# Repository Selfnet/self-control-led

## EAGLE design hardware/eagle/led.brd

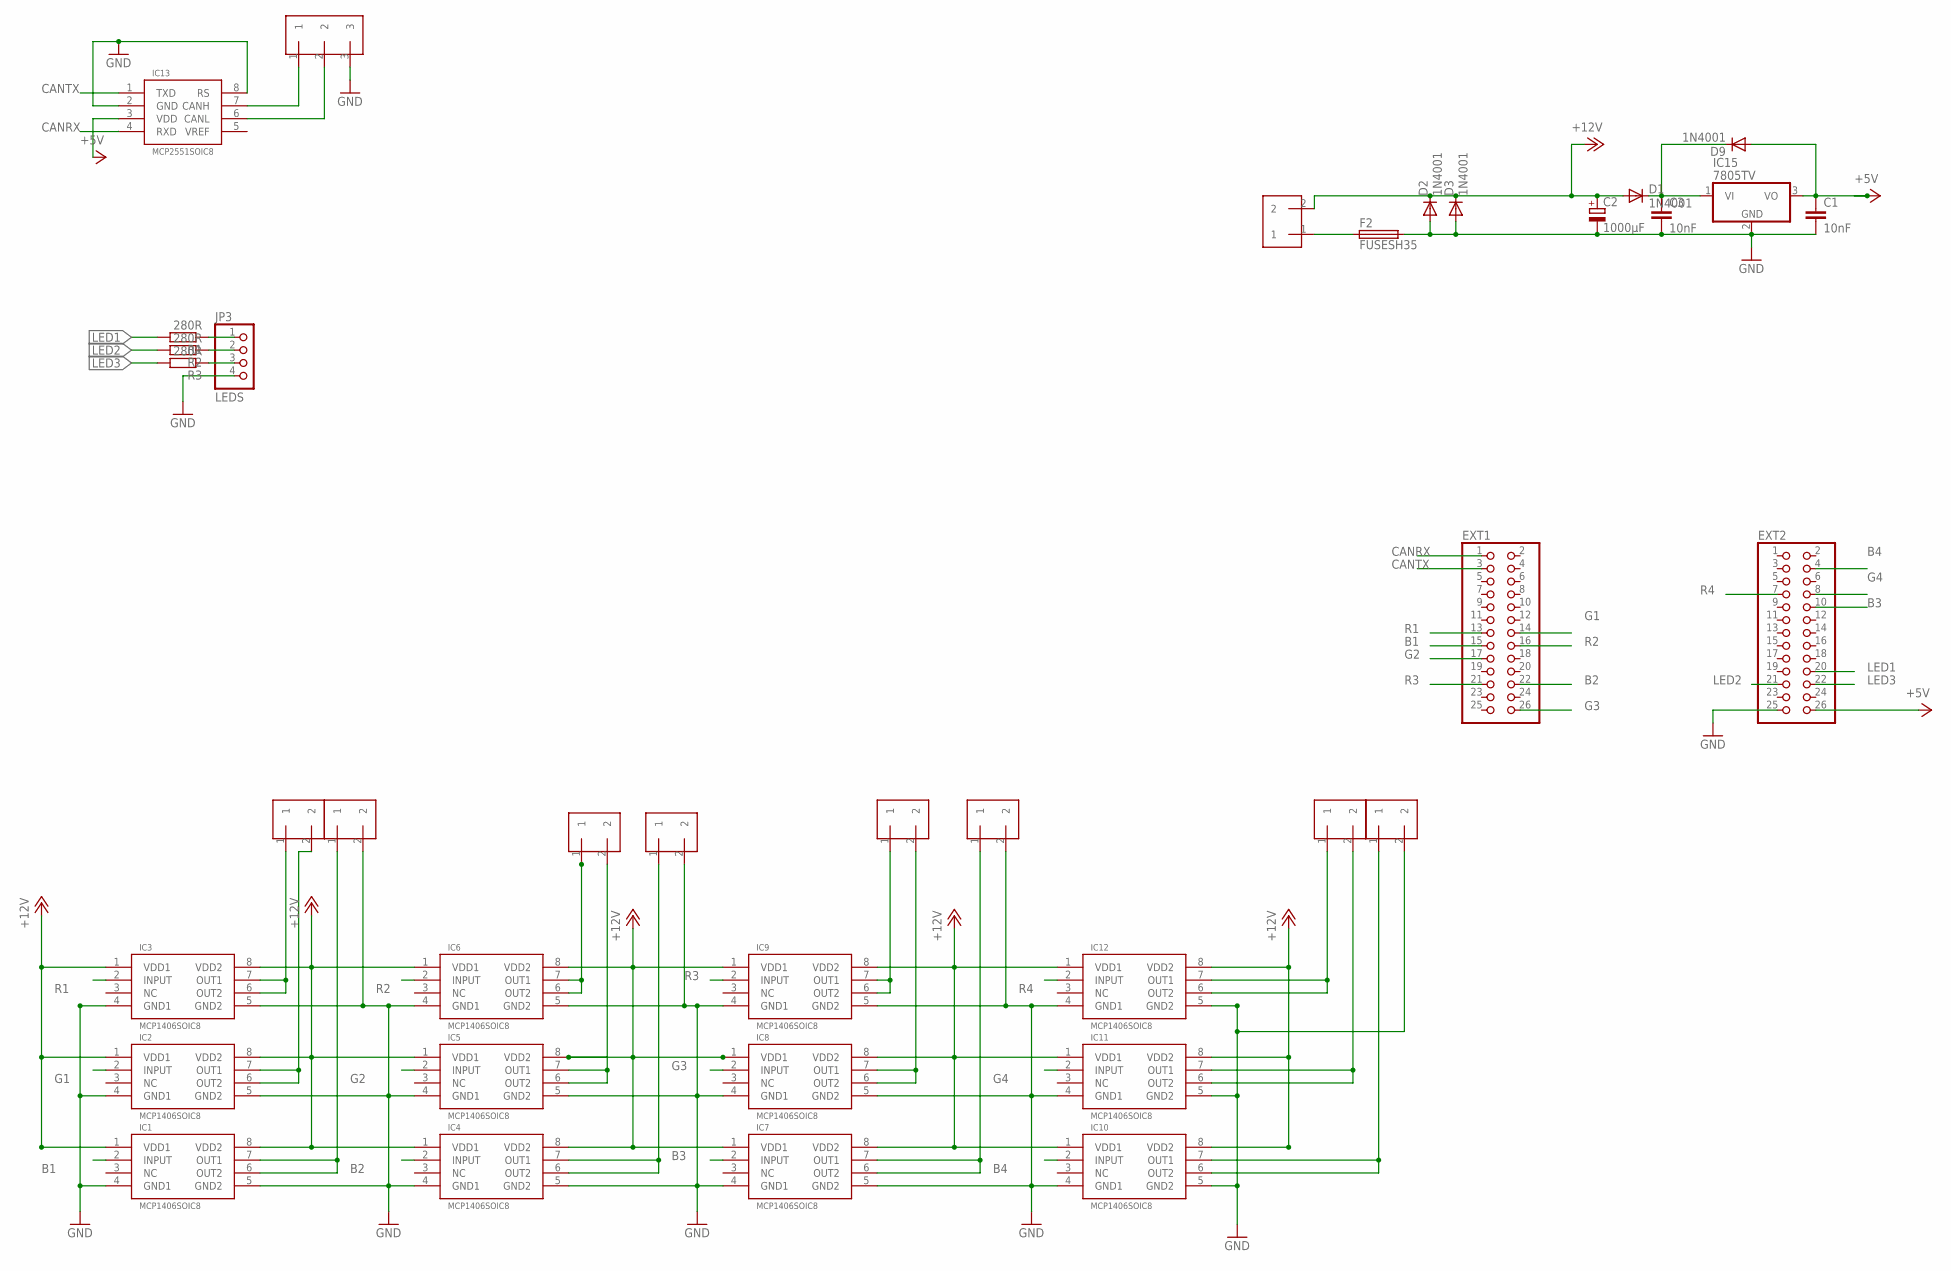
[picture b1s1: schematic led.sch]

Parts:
C1, C3: 10nF; C025-025X050
C2: 1000µF; E5-8,5
D1, D2, D3, D9: 1N4001; MELF-MLL41
EXT1, EXT2: PINHD-2X13; 2X13
F2: FUSESH35; SH25
IC1, IC2, IC3, IC4, IC5, IC6, IC7, IC8, IC9, IC10, IC11, IC12: MCP1406SOIC8; SOIC-08LG
IC13: MCP2551SOIC8; SOIC-08LG
IC15: 7805TV; TO220V
JP3: LEDS; 1X04
R1, R2, R3: 280R; 0204/7
U$1, U$2, U$5, U$6, U$7, U$8, U$9, U$10, U$11: 2KLEMME; W237-102
U$3: 3KLEMME; W237-103

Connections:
+5V: C1.1, D9.A, EXT2.26, IC13.3 (VDD), IC15.3 (VO)
+12V: C2.+, D1.A, D2.C, D3.C, IC1.1 (VDD1), IC1.8 (VDD2), IC2.1 (VDD1), IC2.8 (VDD2), IC3.1 (VDD1), IC3.8 (VDD2), IC4.1 (VDD1), IC4.8 (VDD2), IC5.1 (VDD1), IC5.8 (VDD2), IC6.1 (VDD1), IC6.8 (VDD2), IC7.1 (VDD1), IC7.8 (VDD2), IC8.1 (VDD1), IC8.8 (VDD2), IC9.1 (VDD1), IC9.8 (VDD2), IC10.1 (VDD1), IC10.8 (VDD2), IC11.1 (VDD1), IC11.8 (VDD2), IC12.1 (VDD1), IC12.8 (VDD2), U$1.2
B1: EXT1.15, IC1.2 (INPUT)
B2: EXT1.22, IC4.2 (INPUT)
B3: EXT2.10, IC7.2 (INPUT)
B4: EXT2.4, IC10.2 (INPUT)
CANH: IC13.7 (CANH), U$3.1
CANL: IC13.6 (CANL), U$3.2
CANRX: EXT1.1, IC13.4 (RXD)
CANTX: EXT1.3, IC13.1 (TXD)
G1: EXT1.14, IC2.2 (INPUT)
G2: EXT1.17, IC5.2 (INPUT)
G3: EXT1.26, IC8.2 (INPUT)
G4: EXT2.8, IC11.2 (INPUT)
GND: C1.2, C2.-, C3.2, D2.A, D3.A, EXT2.25, F2.2, IC1.4 (GND1), IC1.5 (GND2), IC2.4 (GND1), IC2.5 (GND2), IC3.4 (GND1), IC3.5 (GND2), IC4.4 (GND1), IC4.5 (GND2), IC5.4 (GND1), IC5.5 (GND2), IC6.4 (GND1), IC6.5 (GND2), IC7.4 (GND1), IC7.5 (GND2), IC8.4 (GND1), IC8.5 (GND2), IC9.4 (GND1), IC9.5 (GND2), IC10.4 (GND1), IC10.5 (GND2), IC11.4 (GND1), IC11.5 (GND2), IC12.4 (GND1), IC12.5 (GND2), IC13.2 (GND), IC13.8 (RS), IC15.2 (GND), JP3.4, U$2.2, U$3.3, U$6.2, U$7.2, U$11.2
LED1: EXT2.20, R1.2
LED2: EXT2.21, R2.2
LED3: EXT2.22, R3.2
unnamed: C3.1, D1.C, D9.C, IC15.1 (VI)
unnamed: F2.1, U$1.1
unnamed: IC3.6 (OUT2), IC3.7 (OUT1), U$5.1
unnamed: IC2.6 (OUT2), IC2.7 (OUT1), U$5.2
unnamed: IC1.6 (OUT2), IC1.7 (OUT1), U$6.1
unnamed: IC6.6 (OUT2), IC6.7 (OUT1), U$10.1
unnamed: IC5.6 (OUT2), IC5.7 (OUT1), U$10.2
unnamed: IC4.6 (OUT2), IC4.7 (OUT1), U$11.1
unnamed: IC9.6 (OUT2), IC9.7 (OUT1), U$8.1
unnamed: IC8.6 (OUT2), IC8.7 (OUT1), U$8.2
unnamed: IC7.6 (OUT2), IC7.7 (OUT1), U$7.1
unnamed: IC12.6 (OUT2), IC12.7 (OUT1), U$9.1
unnamed: IC11.6 (OUT2), IC11.7 (OUT1), U$9.2
unnamed: IC10.6 (OUT2), IC10.7 (OUT1), U$2.1
unnamed: JP3.1, R1.1
unnamed: JP3.2, R2.1
unnamed: JP3.3, R3.1
R1: EXT1.13, IC3.2 (INPUT)
R2: EXT1.16, IC6.2 (INPUT)
R3: EXT1.21, IC9.2 (INPUT)
R4: EXT2.7, IC12.2 (INPUT)

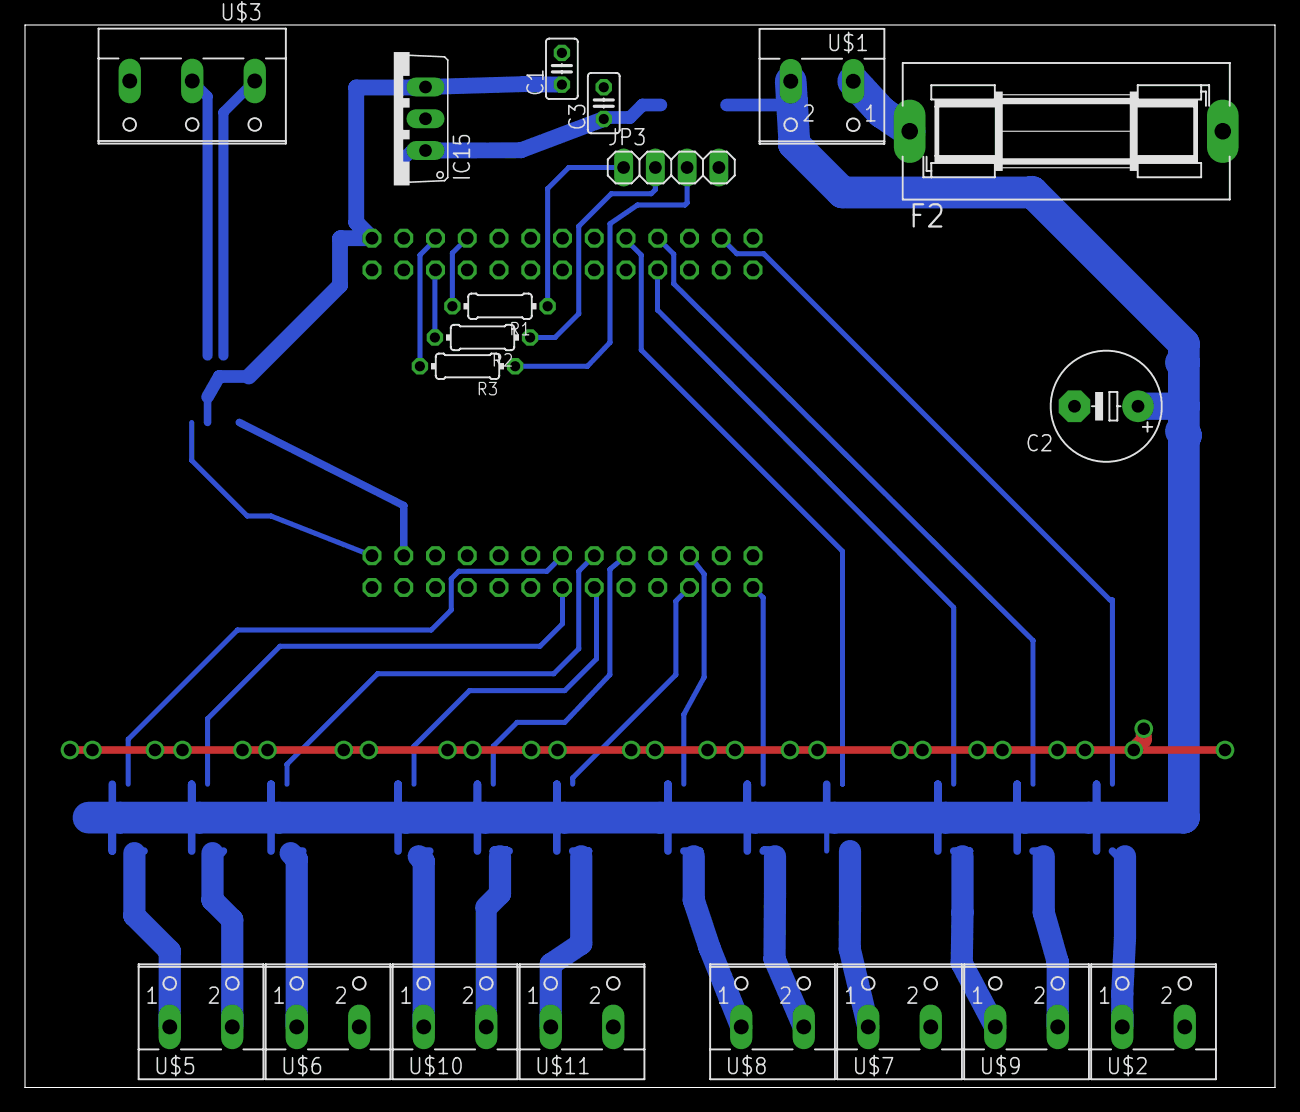
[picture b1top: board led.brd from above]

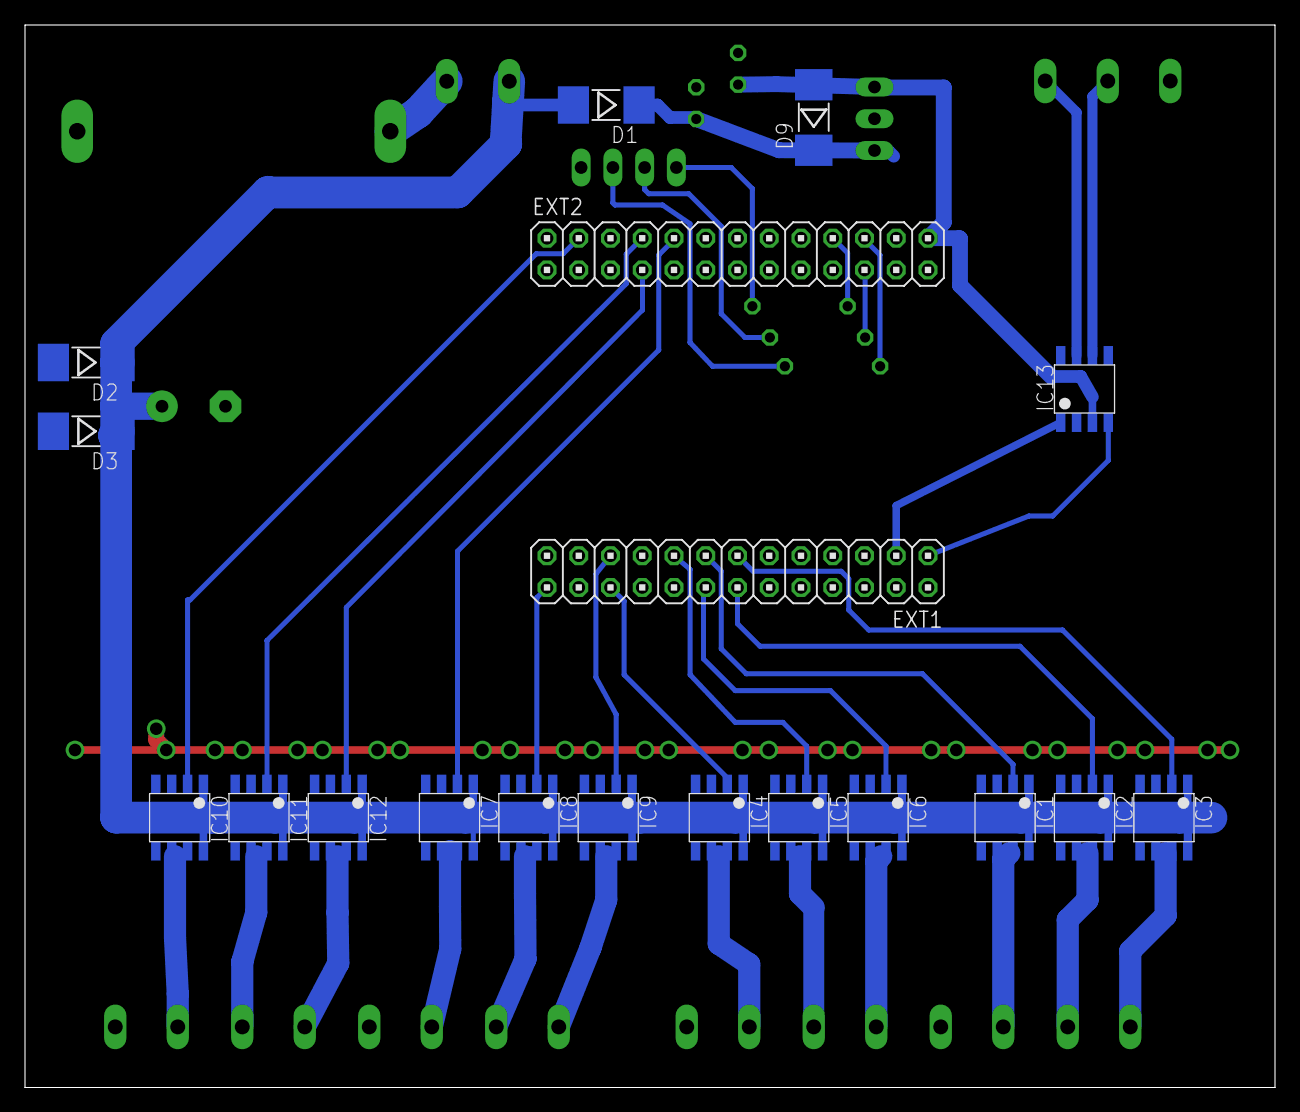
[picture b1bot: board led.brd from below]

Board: 2 copper layers, 100.0 x 85.0 mm, 38 parts (19 on the bottom side), 39 nets.

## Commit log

2013-03-21 inital commit
2013-03-22 funktionierende node - can empfangen und blinken
2013-03-22 Update led_pwm.c
    strobe_police, Mode 7 added
2013-03-24 neue modie + police_strobe merge
2013-03-25 neue can protokol version
2013-03-25 fucking hsv is working!!!!! finaly i stunned the float cast, yeah :)
2013-03-30 new protocol
2013-05-13 hsv color, getColor added
2013-05-13 fixed getLED
2013-05-14 auto fade reanabls every 30min and fade to black after 60min of inactivity
2013-05-20 schaltplan added
2013-05-20 gitignore added
2013-05-21 neue boaerd version + datasheets added
2013-05-22 hardware changed
2013-05-25 neues board nicht fertig geroutet wegen kreuzungen
2013-06-06 nur noch 2 drahtbrücken im layout: TODO buchsen nach löschen ausrichten
2013-06-21 einige datein mal mit commitet da die sonst immer vergessen wurden
